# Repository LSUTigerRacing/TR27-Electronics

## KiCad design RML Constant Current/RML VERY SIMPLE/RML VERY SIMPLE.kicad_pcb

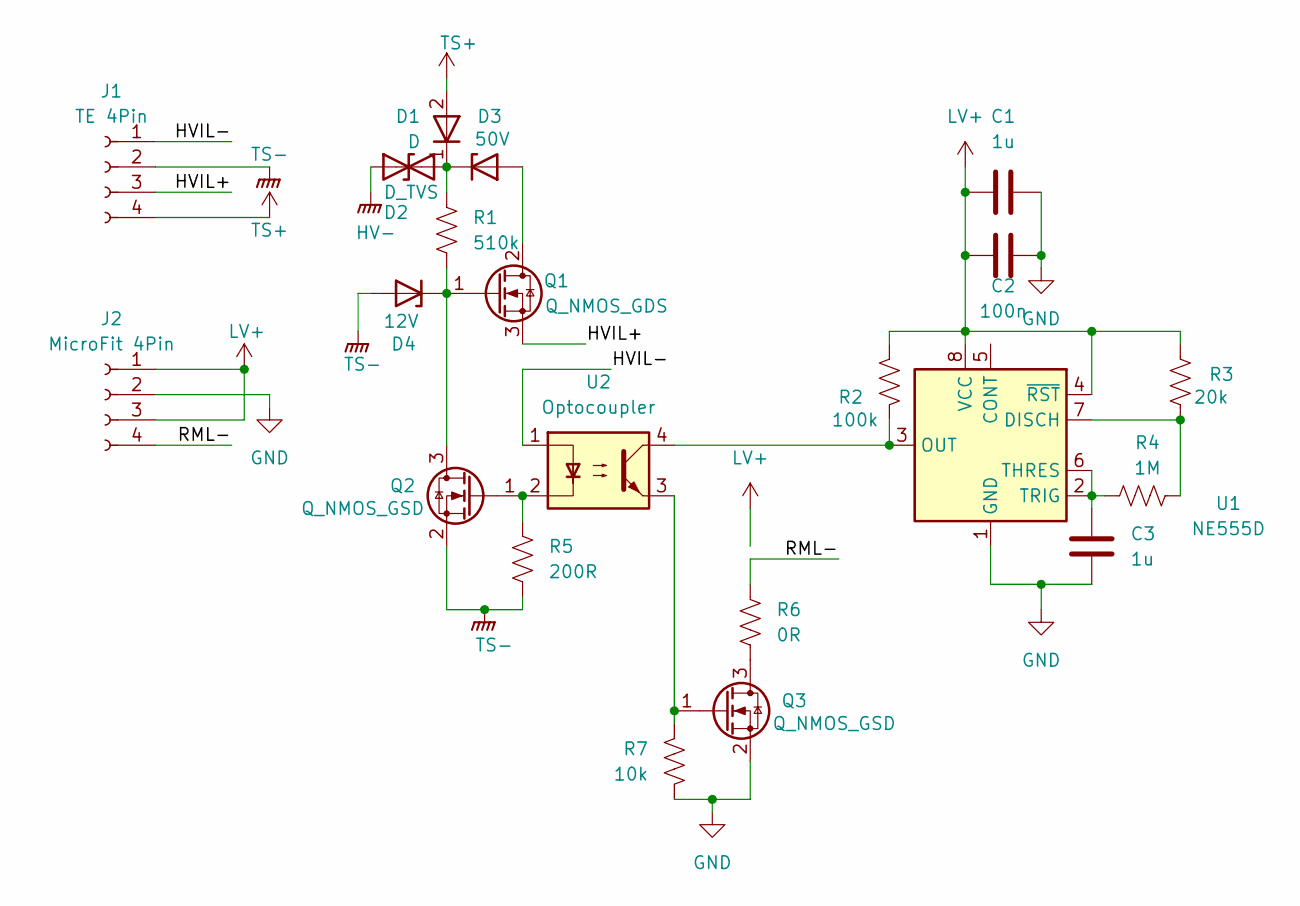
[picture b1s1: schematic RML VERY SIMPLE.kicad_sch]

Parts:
C1, C3: 1u; C_0805_2012Metric; Mouser# 603-AC0805KKX7R9B105; Digikey# 13-AC0805KKX7R9BB105CT-ND
C2: 100n; C_0603_1608Metric; Mouser# 603-AC0603KR9BB104; Digikey# 311-3034-2-ND
D1: D; D_SMA; Mouser# 637-M7
D2: D_TVS; D_SMA; Mouser# 652-SMAJ350CA; Digikey# SMAJ350CALFCT-ND
D3: 50V; D_SOD-123F; Mouser# 771-HPZR-C50X; Digikey# 1727-HPZR-C50XCT-ND
D4: 12V; D_SOD-123F; Mouser# 637-MMSZ5242B; Digikey# 4878-MMSZ5242BCT-ND
J1: TE 4Pin; 214450884; Mouser# 571-2-1445088-4; Digikey# A144905-ND
J2: MicroFit 4Pin; CONN_SD-43045-001_04_MOL_Microfit; Mouser# 538-43045-0400; Digikey# WM1814-ND
Q1: Q_NMOS_GDS; TO-220-3_Horizontal_TabUp; Mouser# 747-IXTP08N50D2; Digikey# 238-IXTP08N50D2-ND
Q2, Q3: Q_NMOS_GSD; SOT-23; Mouser# 637-MMFTN6001; JLC# C151421
R1: 510k; R_1206_3216Metric; Mouser# 667-ERJ-P08J514V; Digikey# P510KALCT-ND
R2: 100k; R_0805_2012Metric; Mouser# 603-RC0805FR-10100KL; Digikey# 13-RC0805FR-10100KLCT-ND
R3: 20k; R_0805_2012Metric; Mouser# 603-AC0805FR-0720KL; Digikey# YAG3708CT-ND
R4: 1M; R_0805_2012Metric; Mouser# 603-RC0805FR-071MP
R5: 200R; R_0805_2012Metric; Mouser# 603-AC0805FR-13200RL
R6: 0R; R_0805_2012Metric; Mouser# 603-RC0805JR-070RL
R7: 10k; R_0805_2012Metric; Mouser# 603-RC0805FR-0710KL
U1: NE555D; SOIC-8_3.9x4.9mm_P1.27mm; Mouser# 595-NE555DR; Digikey# 296-6501-1-ND
U2: Optocoupler; Q_Wurth_WL-OCPT_LSOP4-STANDARD; Mouser# 78-VOLA617A-3X001T

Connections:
/HVIL+: J1.3, Q1.3 (S)
/HVIL-: J1.1, U2.1
/RML-: J2.4, R6.1
GND: C1.2, C2.2, C3.2, J2.2, Q3.2 (S), R7.2, U1.1 (GND)
HV-: D2.1 (A1)
LV+: C1.1, C2.1, J2.1, J2.3, R2.1, R3.1, U1.4 (~RST), U1.8 (VCC)
unnamed: D1.1 (K), D2.2 (A2), D3.1 (K), R1.1
unnamed: D3.2 (A), Q1.2 (D)
unnamed: D4.1 (K), Q1.1 (G), Q2.3 (D), R1.2
unnamed: Q2.1 (G), R5.1, U2.2
unnamed: Q3.3 (D), R6.2
unnamed: Q3.1 (G), R7.1, U2.3
unnamed: R3.2, R4.1, U1.7 (DISCH)
unnamed: R2.2, U1.3 (OUT), U2.4
unnamed: C3.1, R4.2, U1.2 (TRIG), U1.6 (THRES)
TS+: D1.2 (A), J1.4
TS-: D4.2 (A), J1.2, Q2.2 (S), R5.2

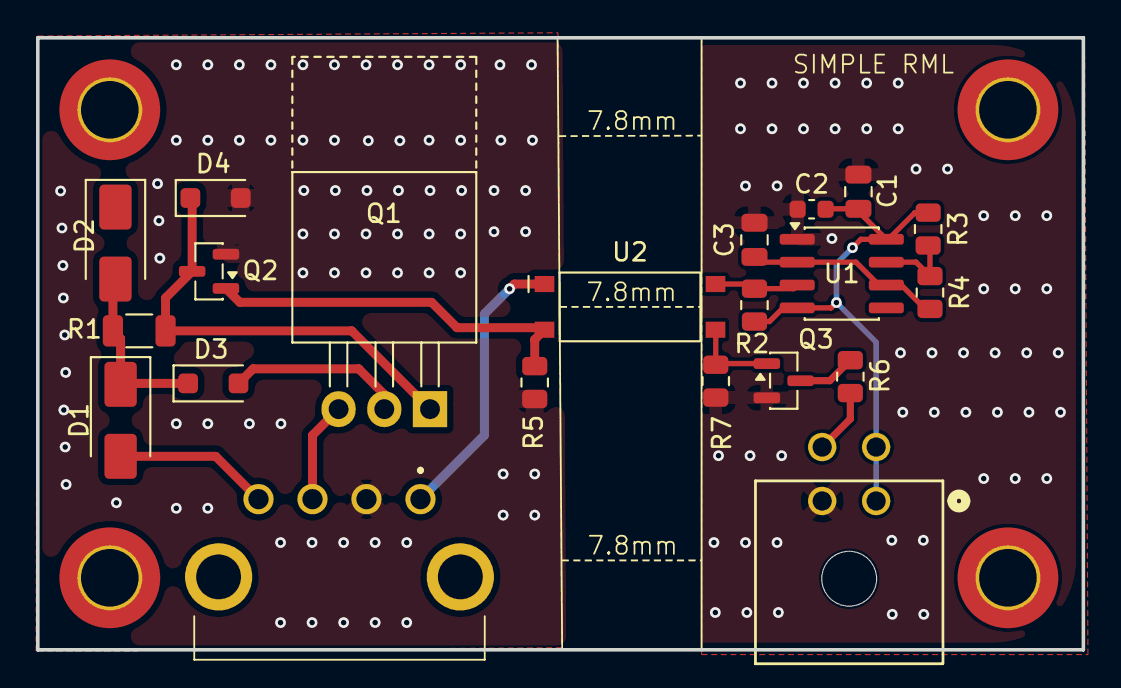
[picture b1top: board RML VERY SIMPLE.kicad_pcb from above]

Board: 2 copper layers, 58.1 x 34.0 mm, 25 parts (0 on the bottom side), 16 nets.

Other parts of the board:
H1, H2, H3, H4: MountingHole; MountingHole_3.2mm_M3_DIN965_Pad_TopOnly

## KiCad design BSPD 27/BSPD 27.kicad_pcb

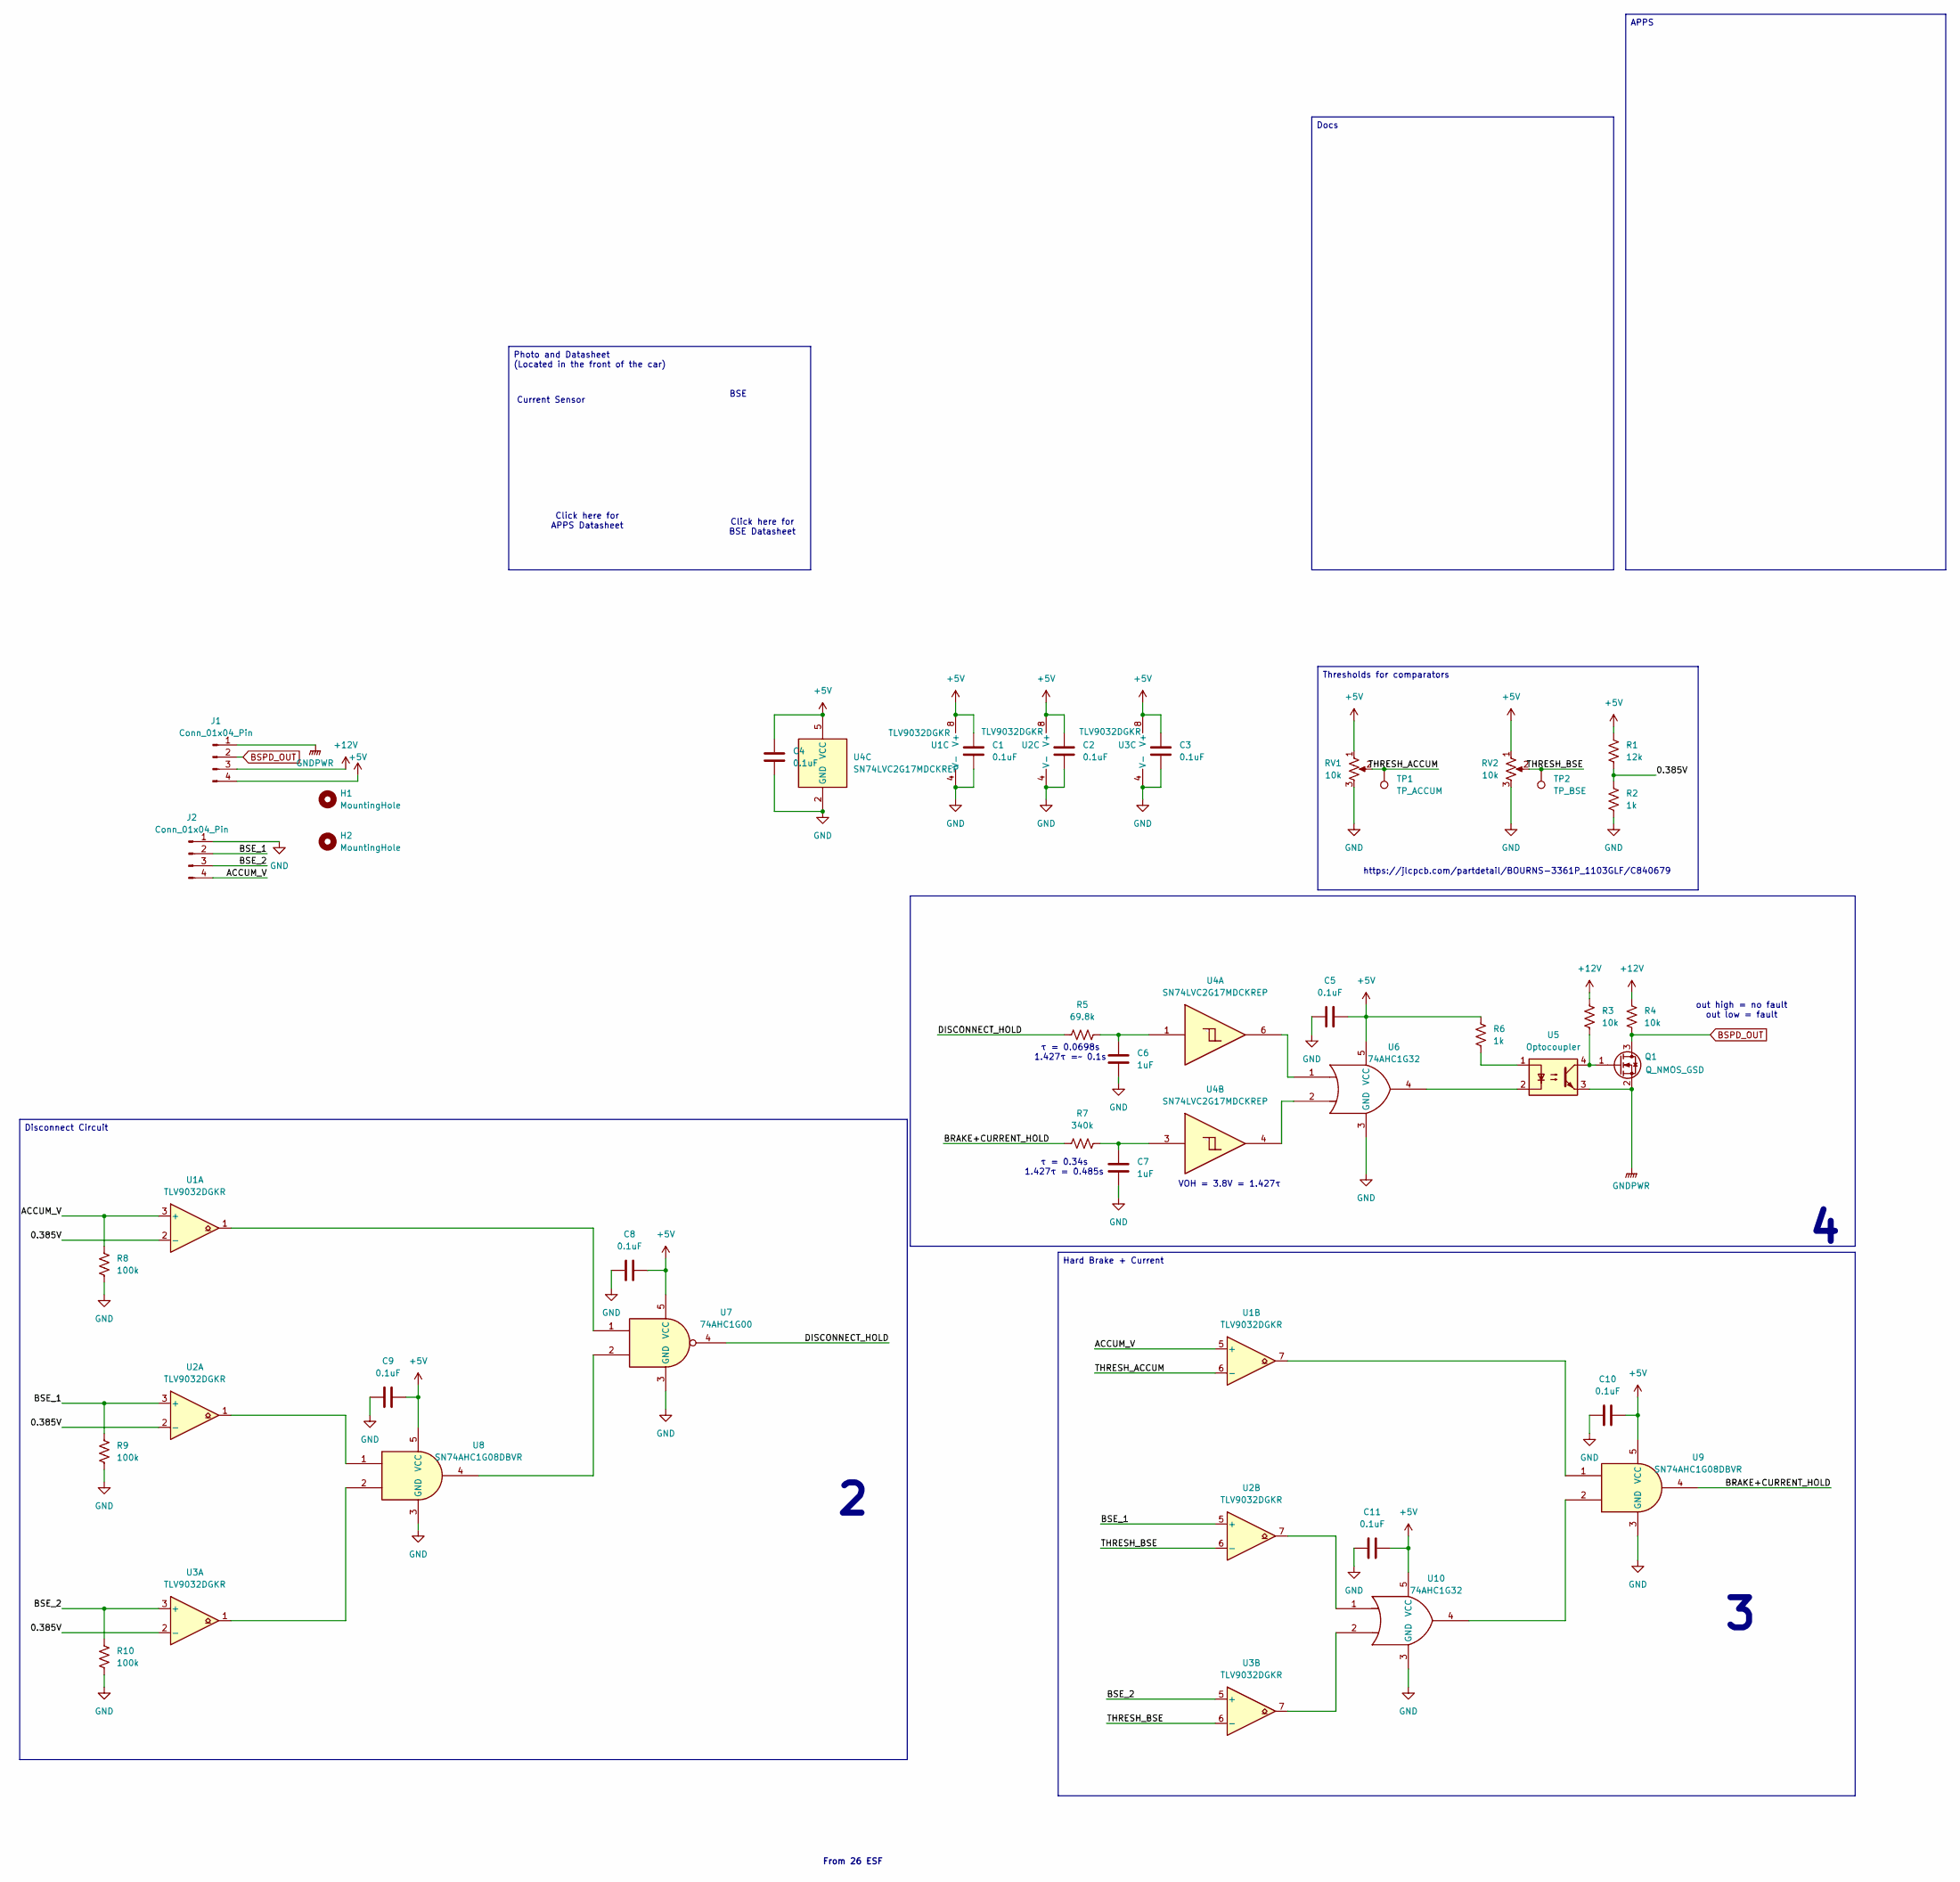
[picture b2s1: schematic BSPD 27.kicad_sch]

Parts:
C1, C2, C3, C4, C5, C8, C9, C10, C11: 0.1uF; C_0603_1608Metric; Mouser# AC0603KRX7R9BB104; JLC# C24497
C6, C7: 1uF; C_0805_2012Metric; Mouser# AC0805KKX7R9BB105; JLC# C782156
H1, H2: MountingHole; MountingHole_3.2mm_M3_DIN965_Pad
J1, J2: Conn_01x04_Pin; SAMTEC_TSW-104-07-L-S; Mouser# N/A; Digikey# N/A
Q1: Q_NMOS_GSD; SOT-23; Mouser# 637-MMFTN6001; JLC# C151421
R1: 12k; R_0805_2012Metric; JLC# C182355
R2: 1k; R_0805_2012Metric; JLC# C230096
R3, R4: 10k; R_0805_2012Metric; JLC# C17414
R5: 69.8k; R_0805_2012Metric; JLC# C230096
R6: 1k; R_0805_2012Metric; Digikey# 311-1.00KCRCT-ND
R7: 340k; R_0805_2012Metric; JLC# C3000590
R8, R9, R10: 100k; R_0805_2012Metric; JLC# C185765
RV1, RV2: 10k; PVG5A103C03B00; Mouser# 81-PVG5A103C03B00; JLC# C48731759
TP1: TP_ACCUM; TestPoint_Pad_D1.5mm
TP2: TP_BSE; TestPoint_Pad_D1.5mm
U1, U2, U3: TLV9032DGKR; SOP65P490X110-8N; Digikey# 296-TLV9032DGKRCT-ND
U4: SN74LVC2G17MDCKREP; SOT-363_SC-70-6; Digikey# 296-22358-1-ND
U5: Optocoupler; SSOP-4_VOS617A_VIS; Digikey# 78-VOS617A-3T
U6, U10: 74AHC1G32; SOT-353_SC-70-5; Mouser# 595-SN74LVC1G32DCKR
U7: 74AHC1G00; SOT-353_SC-70-5; Mouser# 595-SN74LVC1G00DCKR
U8: SN74AHC1G08DBVR; SOT-353_SC-70-5; Mouser# 595-SN74LVC1G08DCKR; JLC# C7467
U9: SN74AHC1G08DBVR; SOT-353_SC-70-5; Mouser# 595-SN74LVC1G11DCKR; JLC# C7467

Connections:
+5V: C1.1, C2.1, C3.1, C4.2, C5.2, C8.2, C9.2, C10.2, C11.2, J1.4, R1.2, R6.1, RV1.1, RV2.1, U1.8 (V+), U2.8 (V+), U3.8 (V+), U4.5 (VCC), U6.5 (VCC), U7.5 (VCC), U8.5 (VCC), U9.5 (VCC), U10.5 (VCC)
+12V: J1.3, R3.1, R4.1
/0.385V: R1.1, R2.2, U1.2 (-), U2.2 (-), U3.2 (-)
/ACCUM_V: J2.4, R8.2, U1.3 (+), U1.5 (+)
/BRAKE+CURRENT_HOLD: R7.1, U9.4
/BSE_1: J2.2, R9.2, U2.3 (+), U2.5 (+)
/BSE_2: J2.3, R10.2, U3.3 (+), U3.5 (+)
/DISCONNECT_HOLD: R5.1, U7.4
/THRESH_ACCUM: RV1.2, TP1.1 (1_1), U1.6 (-)
/THRESH_BSE: RV2.2, TP2.1 (1_1), U2.6 (-), U3.6 (-)
BSPD_OUT: J1.2, Q1.3 (D), R4.2
GND: C1.2, C2.2, C3.2, C4.1, C5.1, C6.2, C7.2, C8.1, C9.1, C10.1, C11.1, J2.1, R2.1, R8.1, R9.1, R10.1, RV1.3, RV2.3, U1.4 (V-), U2.4 (V-), U3.4 (V-), U4.2 (GND), U6.3 (GND), U7.3 (GND), U8.3 (GND), U9.3 (GND), U10.3 (GND)
GNDPWR: J1.1, Q1.2 (S), U5.3
unnamed: C6.1, R5.2, U4.1
unnamed: C7.1, R7.2, U4.3
unnamed: Q1.1 (G), R3.2, U5.4
unnamed: R6.2, U5.1
unnamed: U1.1, U7.1
unnamed: U1.7, U9.1
unnamed: U2.1, U8.1
unnamed: U3.1, U8.2
unnamed: U4.4, U6.2
unnamed: U4.6, U6.1
unnamed: U5.2, U6.4
unnamed: U7.2, U8.4
unnamed: U2.7, U10.1
unnamed: U3.7, U10.2
unnamed: U9.2, U10.4

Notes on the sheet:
Current Sensor
Click here for BSE Datasheet
τ = 0.34s 1.427τ = 0.485s
τ = 0.0698s 1.427τ =~ 0.1s
BSE
out high = no fault out low = fault
VOH = 3.8V = 1.427τ
From 26 ESF
Click here for APPS Datasheet
https://jlcpcb.com/partdetail/BOURNS-3361P_1103GLF/C840679
Hard Brake + Current
Thresholds for comparators
Disconnect Circuit
APPS
Photo and Datasheet (Located in the front of the car)
Docs

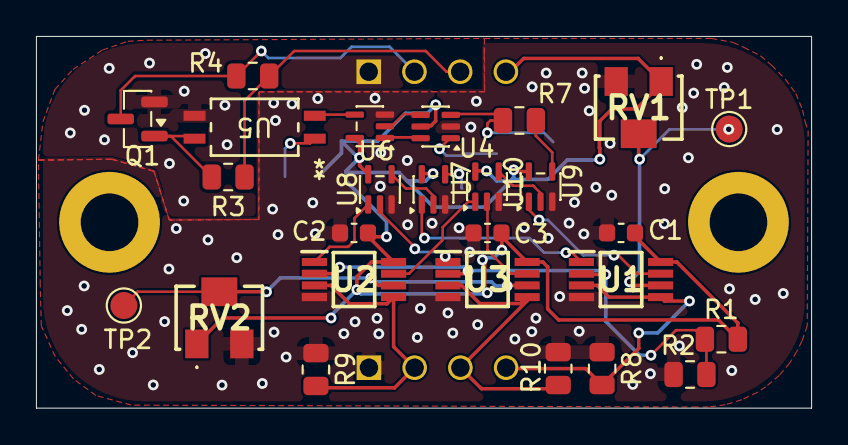
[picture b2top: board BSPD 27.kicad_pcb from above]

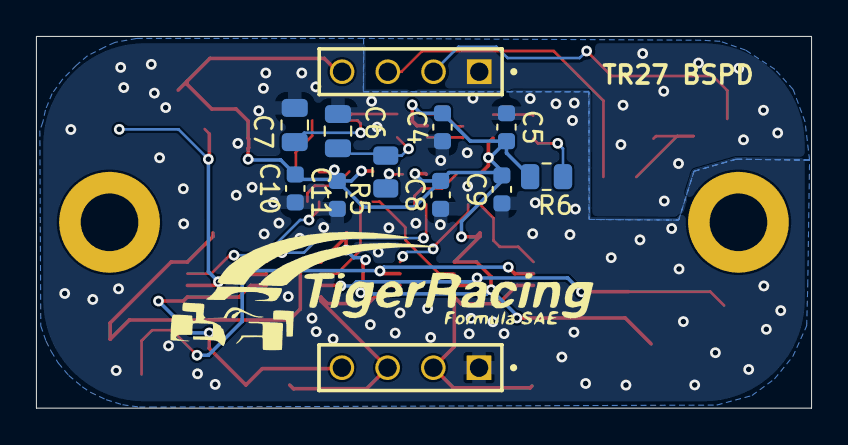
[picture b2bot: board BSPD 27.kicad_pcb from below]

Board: 2 copper layers, 43.1 x 20.7 mm, 40 parts (12 on the bottom side), 28 nets.

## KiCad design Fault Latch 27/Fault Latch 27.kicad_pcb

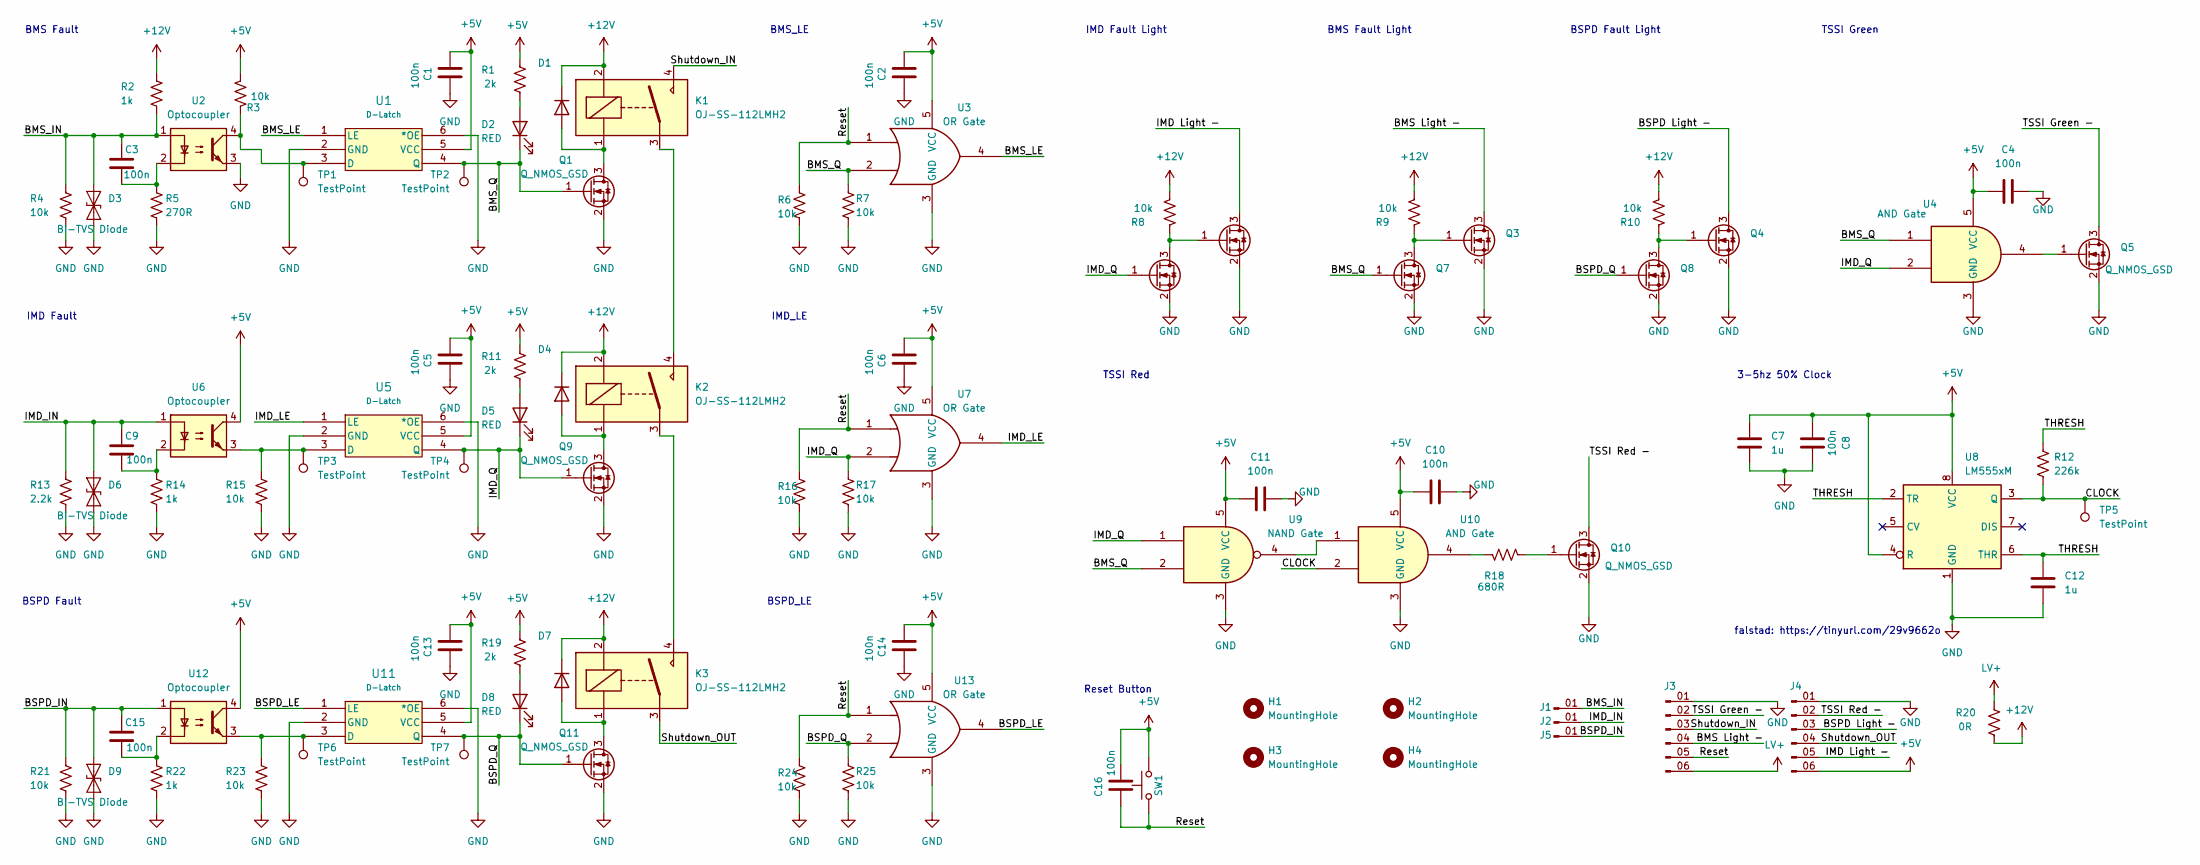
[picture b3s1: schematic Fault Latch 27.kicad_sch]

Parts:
C1, C2, C5, C6, C13, C14, C16: 100n; C_0603_1608Metric; Mouser# 603-AC0603KR9BB104; JLC# C1591
C3, C4, C9, C10, C11, C15: 100n; C_0603_1608Metric; Mouser# 603-AC0603KR9BB104; JLC# C133086
C7, C12: 1u; C_0805_2012Metric; Mouser# 603-AC0805KKX7R9B105; JLC# C1592
C8: 100n; C_0603_1608Metric; Mouser# 603-AC0603KR9BB104; JLC# C1590
D1, D4, D7: D_SOD-323; Mouser# N/A; Digikey# 5399-1N4007WSCT-ND
D2, D5, D8: RED; LED_0805_2012Metric_Pad1.15x1.40mm_HandSolder; Digikey# 475-LSR976-NR-1CT-ND
D3, D6, D9: Bi-TVS Diode; D_SOD-523; Mouser# 750-CPDUR12V-HF; JLC# C2443698
H1, H2, H3, H4: MountingHole; MountingHole_3.2mm_M3_DIN965_Pad
J1, J2, J5: Conn_01x01_Pin; SAMTEC_TSW-101-07-L-S
J3, J4: Conn_01x06_Pin; SAMTEC_TSW-103-07-L-D
K1, K2, K3: OJ-SS-112LMH2; OJSS112LMH2; Mouser# 655-OJ-SS-112LMH2
Q1, Q2, Q3, Q4, Q5, Q6, Q7, Q8, Q9, Q10, Q11: Q_NMOS_GSD; SOT-23; Mouser# 637-MMFTN6001; JLC# C151421
R1, R11, R19: 2k; R_0805_2012Metric; Mouser# 603-RC0805FR-072KL; JLC# C137097
R2, R14, R22: 1k; R_0805_2012Metric; JLC# C137088
R3, R4, R6, R7, R8, R9, R10, R15, R16, R17, R21, R23, R24, R25: 10k; R_0805_2012Metric; JLC# C137088
R5: 270R; R_0805_2012Metric
R12: 226k; R_0805_2012Metric; Mouser# 603-RC0805FR-07226KL; JLC# C17900
R13: 2.2k; R_1206_3216Metric; Mouser# 660-SG73P2BTTD2201F; JLC# C137088
R18: 680R; R_0805_2012Metric; Mouser# 603-RC0805FR-07680RL; JLC# C137071
R20: 0R; R_0805_2012Metric; Digikey# 311-0.0ARCT-ND
SW1: SW_Omron_B3FS; SW_SPST_Omron_B3FS-100xP; Mouser# 653-B3FS-1000P; JLC# C271750
TP1, TP2, TP3, TP4, TP5, TP6, TP7: TestPoint; TestPoint_Pad_1.0x1.0mm
U1, U5, U11: D-Latch; SOT-363_SC-70-6; Digikey# 296-18775-1-ND
U2, U6, U12: Optocoupler; SSOP-4_VOS617A_VIS; Digikey# VOS617A-3TTR-ND
U3, U7, U13: OR Gate; SOT-353_SC-70-5; Mouser# 595-SN74LVC1G32DCKR
U4, U10: AND Gate; SOT-353_SC-70-5; Mouser# 595-SN74LVC1G11DCKR; JLC# C7467
U8: LM555xM; SOIC-8_3.9x4.9mm_P1.27mm; Mouser# 926-LMC555CMX/NOPB; JLC# C90760
U9: NAND Gate; SOT-353_SC-70-5; Mouser# 595-SN74LVC1G00DCKR

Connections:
+5V: C1.1, C2.1, C4.2, C5.1, C6.1, C7.1, C8.1, C10.2, C11.2, C13.1, C14.1, C16.1, J4.06 (Pin_6), R1.2, R3.1, R11.2, R19.2, SW1.2, U1.5 (VCC), U3.5 (VCC), U4.5 (VCC), U5.5 (VCC), U6.4, U7.5 (VCC), U8.4 (R), U8.8 (VCC), U9.5 (VCC), U10.5 (VCC), U11.5 (VCC), U12.4, U13.5 (VCC)
+12V: D1.1 (K), D4.1 (K), D7.1 (K), K1.2, K2.2, K3.2, R2.2, R8.1, R9.1, R10.1, R20.1
/BMS Light -: J3.04 (Pin_4), Q3.3 (D)
/BMS_IN: C3.1, D3.2 (A2), J1.01 (Pin_1_01), R2.1, R4.2, U2.1
/BMS_LE: U1.1 (LE), U3.4
/BMS_Q: D2.1 (K), Q1.1 (G), Q7.1 (G), R7.2, TP2.1 (1_1), U1.4 (Q), U3.2, U4.1, U9.2
/BSPD Light -: J4.03 (Pin_3), Q4.3 (D)
/BSPD_IN: C15.1, D9.2 (A2), J5.01 (Pin_1_01), R21.2, U12.1
/BSPD_LE: U11.1 (LE), U13.4
/BSPD_Q: D8.1 (K), Q8.1 (G), Q11.1 (G), R25.2, TP7.1 (1_1), U11.4 (Q), U13.2
/CLOCK: R12.2, TP5.1 (1_1), U8.3 (Q), U10.2
/IMD Light -: J4.05 (Pin_5), Q2.3 (D)
/IMD_IN: C9.1, D6.2 (A2), J2.01 (Pin_1_01), R13.2, U6.1
/IMD_LE: U5.1 (LE), U7.4
/IMD_Q: D5.1 (K), Q6.1 (G), Q9.1 (G), R17.2, TP4.1 (1_1), U4.2, U5.4 (Q), U7.2, U9.1
/Reset: C16.2, J3.05 (Pin_5), R6.2, R16.2, R24.2, SW1.1, U3.1, U7.1, U13.1
/Shutdown_IN: J3.03 (Pin_3), K1.4
/Shutdown_OUT: J4.04 (Pin_4), K3.3
/THRESH: C12.1, R12.1, U8.2 (TR), U8.6 (THR)
/TSSI Green -: J3.02 (Pin_2), Q5.3 (D)
/TSSI Red -: J4.02 (Pin_2), Q10.3 (D)
GND: C1.2, C2.2, C4.1, C5.2, C6.2, C7.2, C8.2, C10.1, C11.1, C12.2, C13.2, C14.2, D3.1 (A1), D6.1 (A1), D9.1 (A1), J3.01 (Pin_1), J4.01 (Pin_1), Q1.2 (S), Q2.2 (S), Q3.2 (S), Q4.2 (S), Q5.2 (S), Q6.2 (S), Q7.2 (S), Q8.2 (S), Q9.2 (S), Q10.2 (S), Q11.2 (S), R4.1, R5.1, R6.1, R7.1, R13.1, R14.1, R15.1, R16.1, R17.1, R21.1, R22.1, R23.1, R24.1, R25.1, U1.2 (GND), U1.6 (*OE), U2.3, U3.3 (GND), U4.3 (GND), U5.2 (GND), U5.6 (*OE), U7.3 (GND), U8.1 (GND), U9.3 (GND), U10.3 (GND), U11.2 (GND), U11.6 (*OE), U13.3 (GND)
LV+: J3.06 (Pin_6), R20.2
unnamed: C3.2, R5.2, U2.2
unnamed: C9.2, R14.2, U6.2
unnamed: C15.2, R22.2, U12.2
unnamed: D1.2 (A), K1.1, Q1.3 (D)
unnamed: D2.2 (A), R1.1
unnamed: D4.2 (A), K2.1, Q9.3 (D)
unnamed: D5.2 (A), R11.1
unnamed: D7.2 (A), K3.1, Q11.3 (D)
unnamed: D8.2 (A), R19.1
unnamed: K1.3, K2.4
unnamed: K2.3, K3.4
unnamed: Q2.1 (G), Q6.3 (D), R8.2
unnamed: Q3.1 (G), Q7.3 (D), R9.2
unnamed: Q4.1 (G), Q8.3 (D), R10.2
unnamed: Q5.1 (G), U4.4
unnamed: Q10.1 (G), R18.1
unnamed: R18.2, U10.4
unnamed: R3.2, TP1.1 (1_1), U1.3 (D), U2.4
unnamed: R15.2, TP3.1 (1_1), U5.3 (D), U6.3
unnamed: U9.4, U10.1
unnamed: R23.2, TP6.1 (1_1), U11.3 (D), U12.3

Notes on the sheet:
IMD Fault
BSPD Fault Light
TSSI Red
BMS Fault
Reset Button
falstad: https://tinyurl.com/29v9662o
BSPD_LE
TSSI Green
IMD Fault Light
3-5hz 50% Clock
BMS_LE
BSPD Fault
BMS Fault Light
IMD_LE

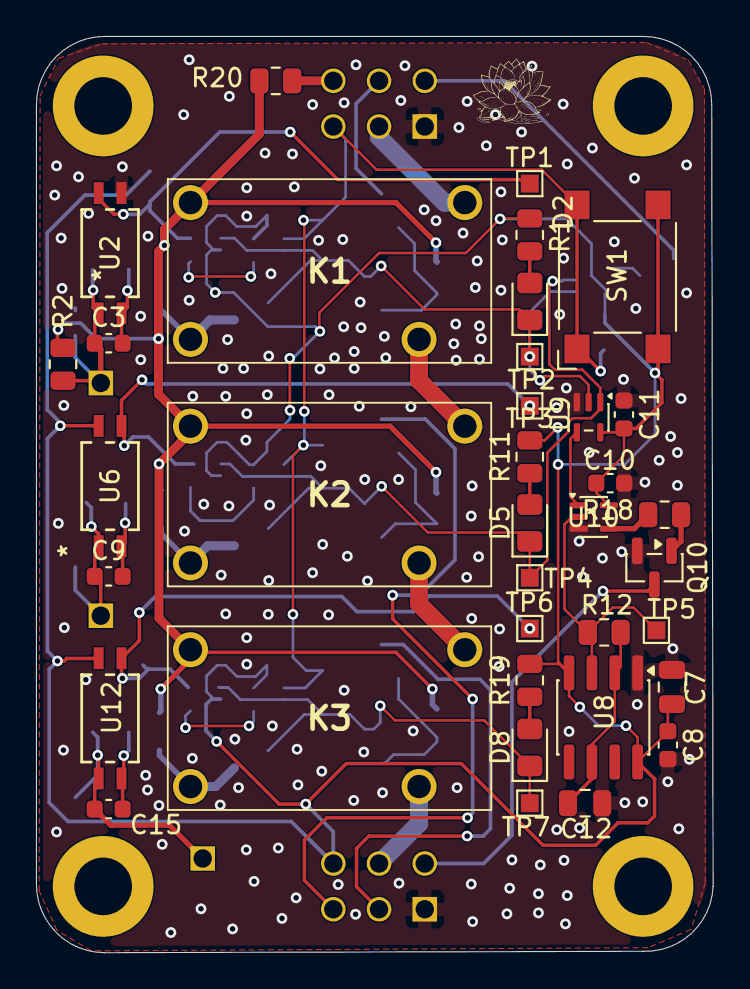
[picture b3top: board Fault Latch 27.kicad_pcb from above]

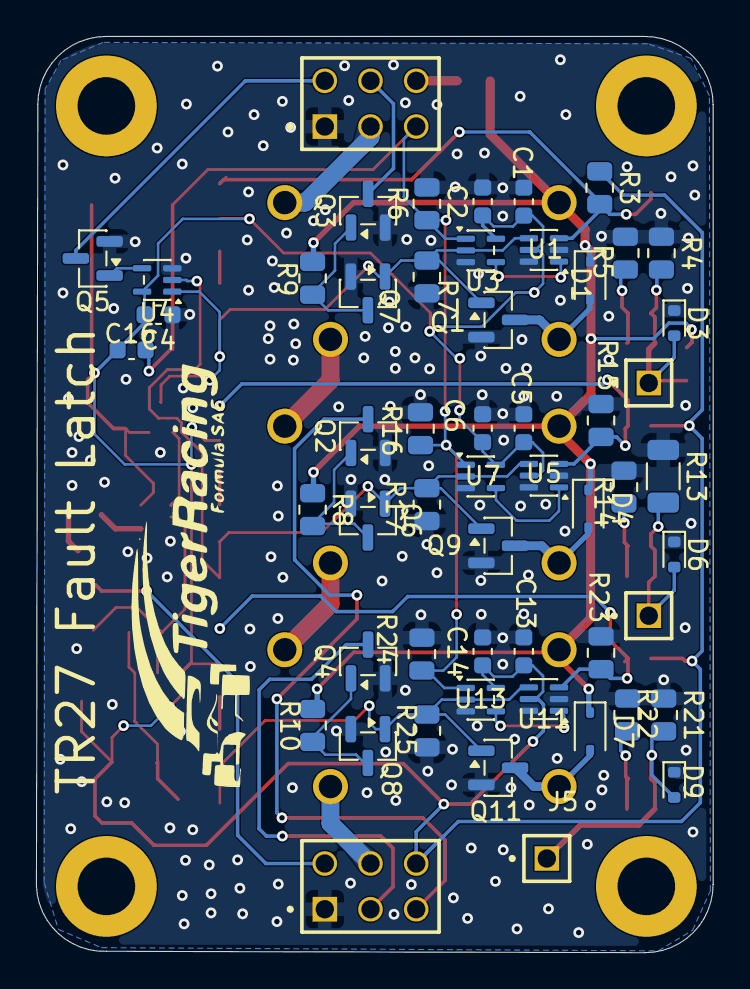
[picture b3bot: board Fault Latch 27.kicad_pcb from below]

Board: 2 copper layers, 37.6 x 50.9 mm, 94 parts (54 on the bottom side), 44 nets.

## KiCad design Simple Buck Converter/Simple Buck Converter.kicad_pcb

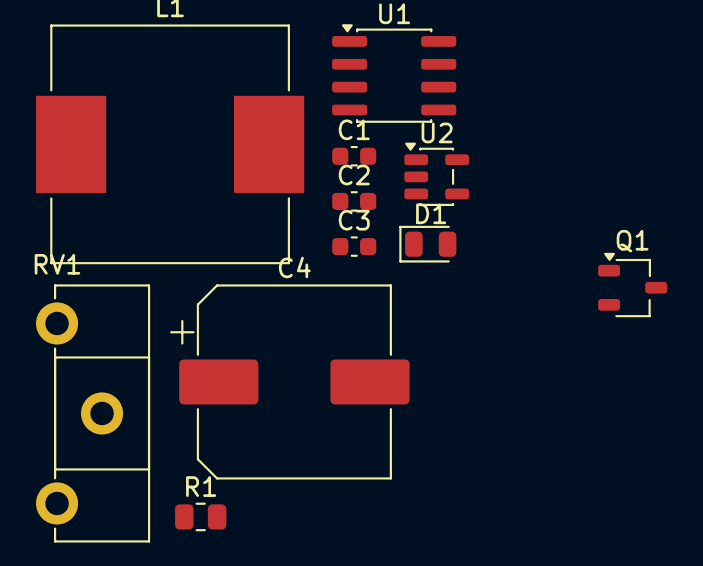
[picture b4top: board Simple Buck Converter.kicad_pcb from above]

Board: 2 copper layers, 11 parts (0 on the bottom side), 8 nets, no tracks yet.

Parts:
C1: 30nF; C_0603_1608Metric
C2, C3: 100nF; C_0603_1608Metric
C4: 100uF; CP_Elec_10x10.5
D1: D; D_0805_2012Metric
L1: 1H; L_Neosid_SM-NE127_HandSoldering
Q1: Q_NMOS; TSOT-23
R1: 10k; R_0805_2012Metric
RV1: 10k; Potentiometer_ACP_CA14-H2,5_Horizontal
U1: LM555xM; SOIC-8_3.9x4.9mm_P1.27mm
U2: LM397; SOT-23-5

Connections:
+12V: C2.1, C3.1, RV1.1, U1.4 (~RST), U1.8 (VCC), U2.5 (V+)
/555Out: R1.2, U1.3 (OUT), U2.3 (+)
/Converter+: C4.1, L1.2
GND: C1.2, C2.2, C3.2, C4.2, D1.2 (A), RV1.3, U1.1 (GND), U2.2 (V-)
unnamed: D1.1 (K), L1.1
unnamed: R1.1, U1.7 (DISCH)
unnamed: C1.1, U1.2 (TRIG), U1.6 (THRES)
unnamed: RV1.2, U2.1 (-)

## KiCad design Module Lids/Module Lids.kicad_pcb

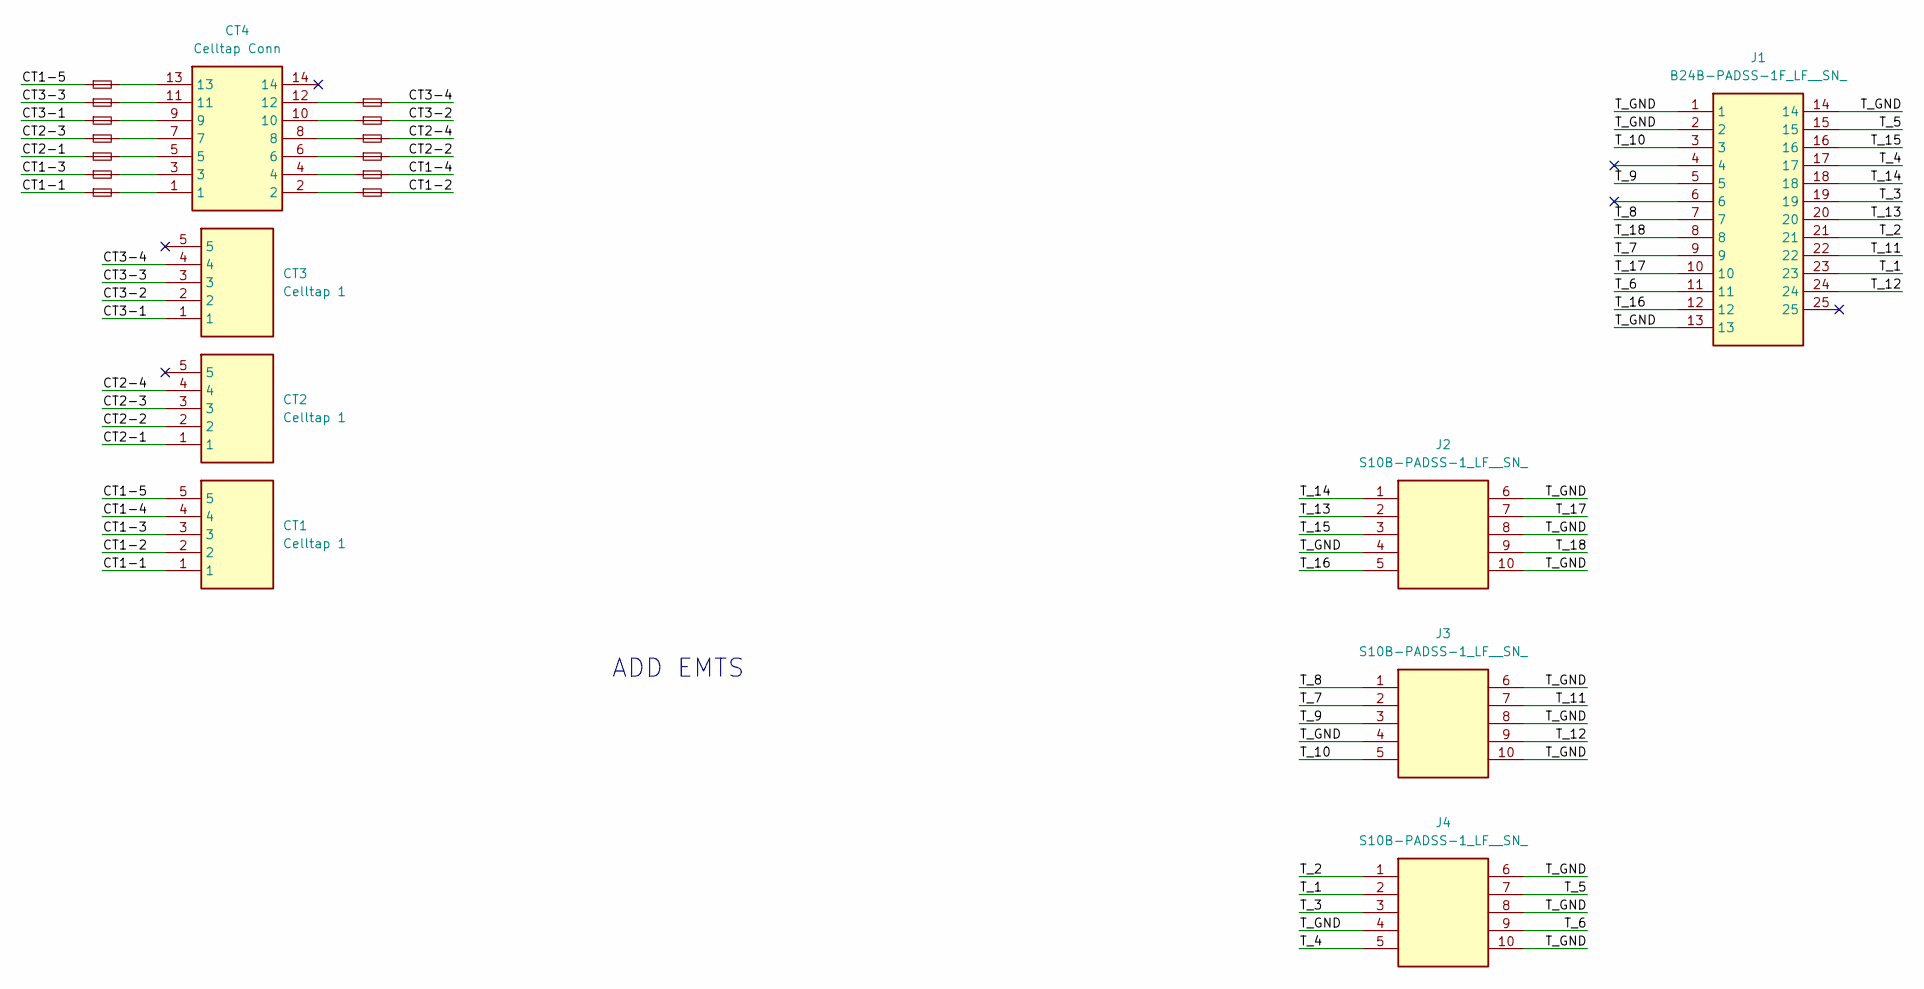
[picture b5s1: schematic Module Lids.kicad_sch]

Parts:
CT1, CT2, CT3: Celltap 1; 5-Pin-Molex; Mouser Part Number 538-215760-1005
CT4: Celltap Conn; 14-Pin-Molex; Mouser Part Number 538-206832-1401
F1, F2, F3, F4, F5, F6, F7, F8, F9, F10, F11, F12, F13: Fuse_Small; Fuse_1206_3216Metric_Pad1.42x1.75mm_HandSolder
J1: B24B-PADSS-1F_LF__SN_; 24-Pin-JST; Mouser Part Number 306-B24BPADSS1FLFSN
J2, J3, J4: S10B-PADSS-1_LF__SN_; 10-Pin-JST; Mouser Part Number 306-S10BPADSS1LFSN

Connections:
/CT1-1: CT1.1, F1.1
/CT1-2: CT1.2, F2.2
/CT1-3: CT1.3, F3.1
/CT1-4: CT1.4, F4.2
/CT1-5: CT1.5, F13.1
/CT2-1: CT2.1, F5.1
/CT2-2: CT2.2, F6.2
/CT2-3: CT2.3, F7.1
/CT2-4: CT2.4, F8.2
/CT3-1: CT3.1, F9.1
/CT3-2: CT3.2, F10.2
/CT3-3: CT3.3, F11.1
/CT3-4: CT3.4, F12.2
/T_1: J1.23, J4.2
/T_2: J1.21, J4.1
/T_3: J1.19, J4.3
/T_4: J1.17, J4.5
/T_5: J1.15, J4.7
/T_6: J1.11, J4.9
/T_7: J1.9, J3.2
/T_8: J1.7, J3.1
/T_9: J1.5, J3.3
/T_10: J1.3, J3.5
/T_11: J1.22, J3.7
/T_12: J1.24, J3.9
/T_13: J1.20, J2.2
/T_14: J1.18, J2.1
/T_15: J1.16, J2.3
/T_16: J1.12, J2.5
/T_17: J1.10, J2.7
/T_18: J1.8, J2.9
/T_GND: J1.1, J1.2, J1.13, J1.14, J2.4, J2.6, J2.8, J2.10, J3.4, J3.6, J3.8, J3.10, J4.4, J4.6, J4.8, J4.10
unnamed: CT4.1, F1.2
unnamed: CT4.2, F2.1
unnamed: CT4.3, F3.2
unnamed: CT4.4, F4.1
unnamed: CT4.5, F5.2
unnamed: CT4.6, F6.1
unnamed: CT4.7, F7.2
unnamed: CT4.8, F8.1
unnamed: CT4.9, F9.2
unnamed: CT4.10, F10.1
unnamed: CT4.11, F11.2
unnamed: CT4.12, F12.1
unnamed: CT4.13, F13.2

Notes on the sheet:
ADD EMTS

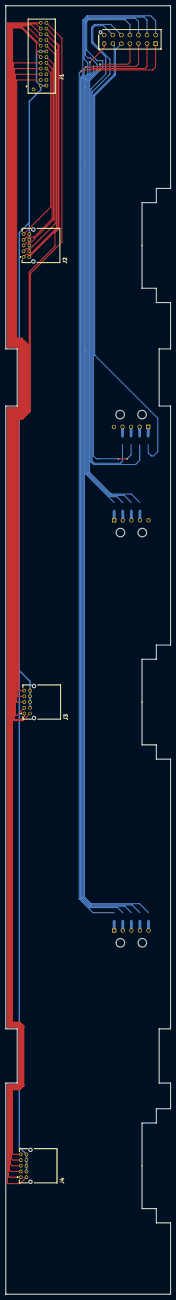
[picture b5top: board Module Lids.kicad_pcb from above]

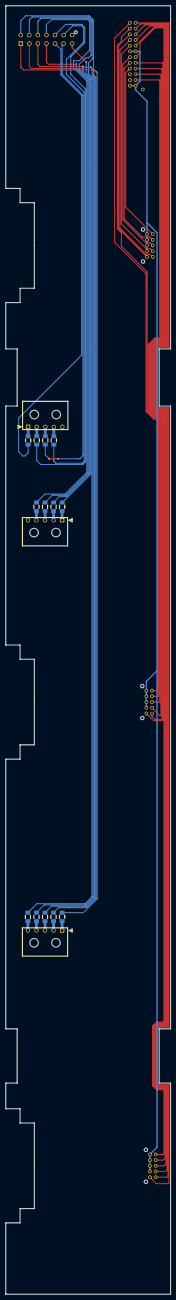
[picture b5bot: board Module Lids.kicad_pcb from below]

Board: 2 copper layers, 57.8 x 451.5 mm, 21 parts (16 on the bottom side), 45 nets.
